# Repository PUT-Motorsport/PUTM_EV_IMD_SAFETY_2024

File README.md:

# Insulation Monitoring Device driver

A driver for Bender ISOMETER IR155-3203 to comply with FSG Rules 25' about latching, and only hard-wired electronics.
As per September 2025 in PMX Malta it relies only on Bender "IMD OK" signal, no PWM reading part needed

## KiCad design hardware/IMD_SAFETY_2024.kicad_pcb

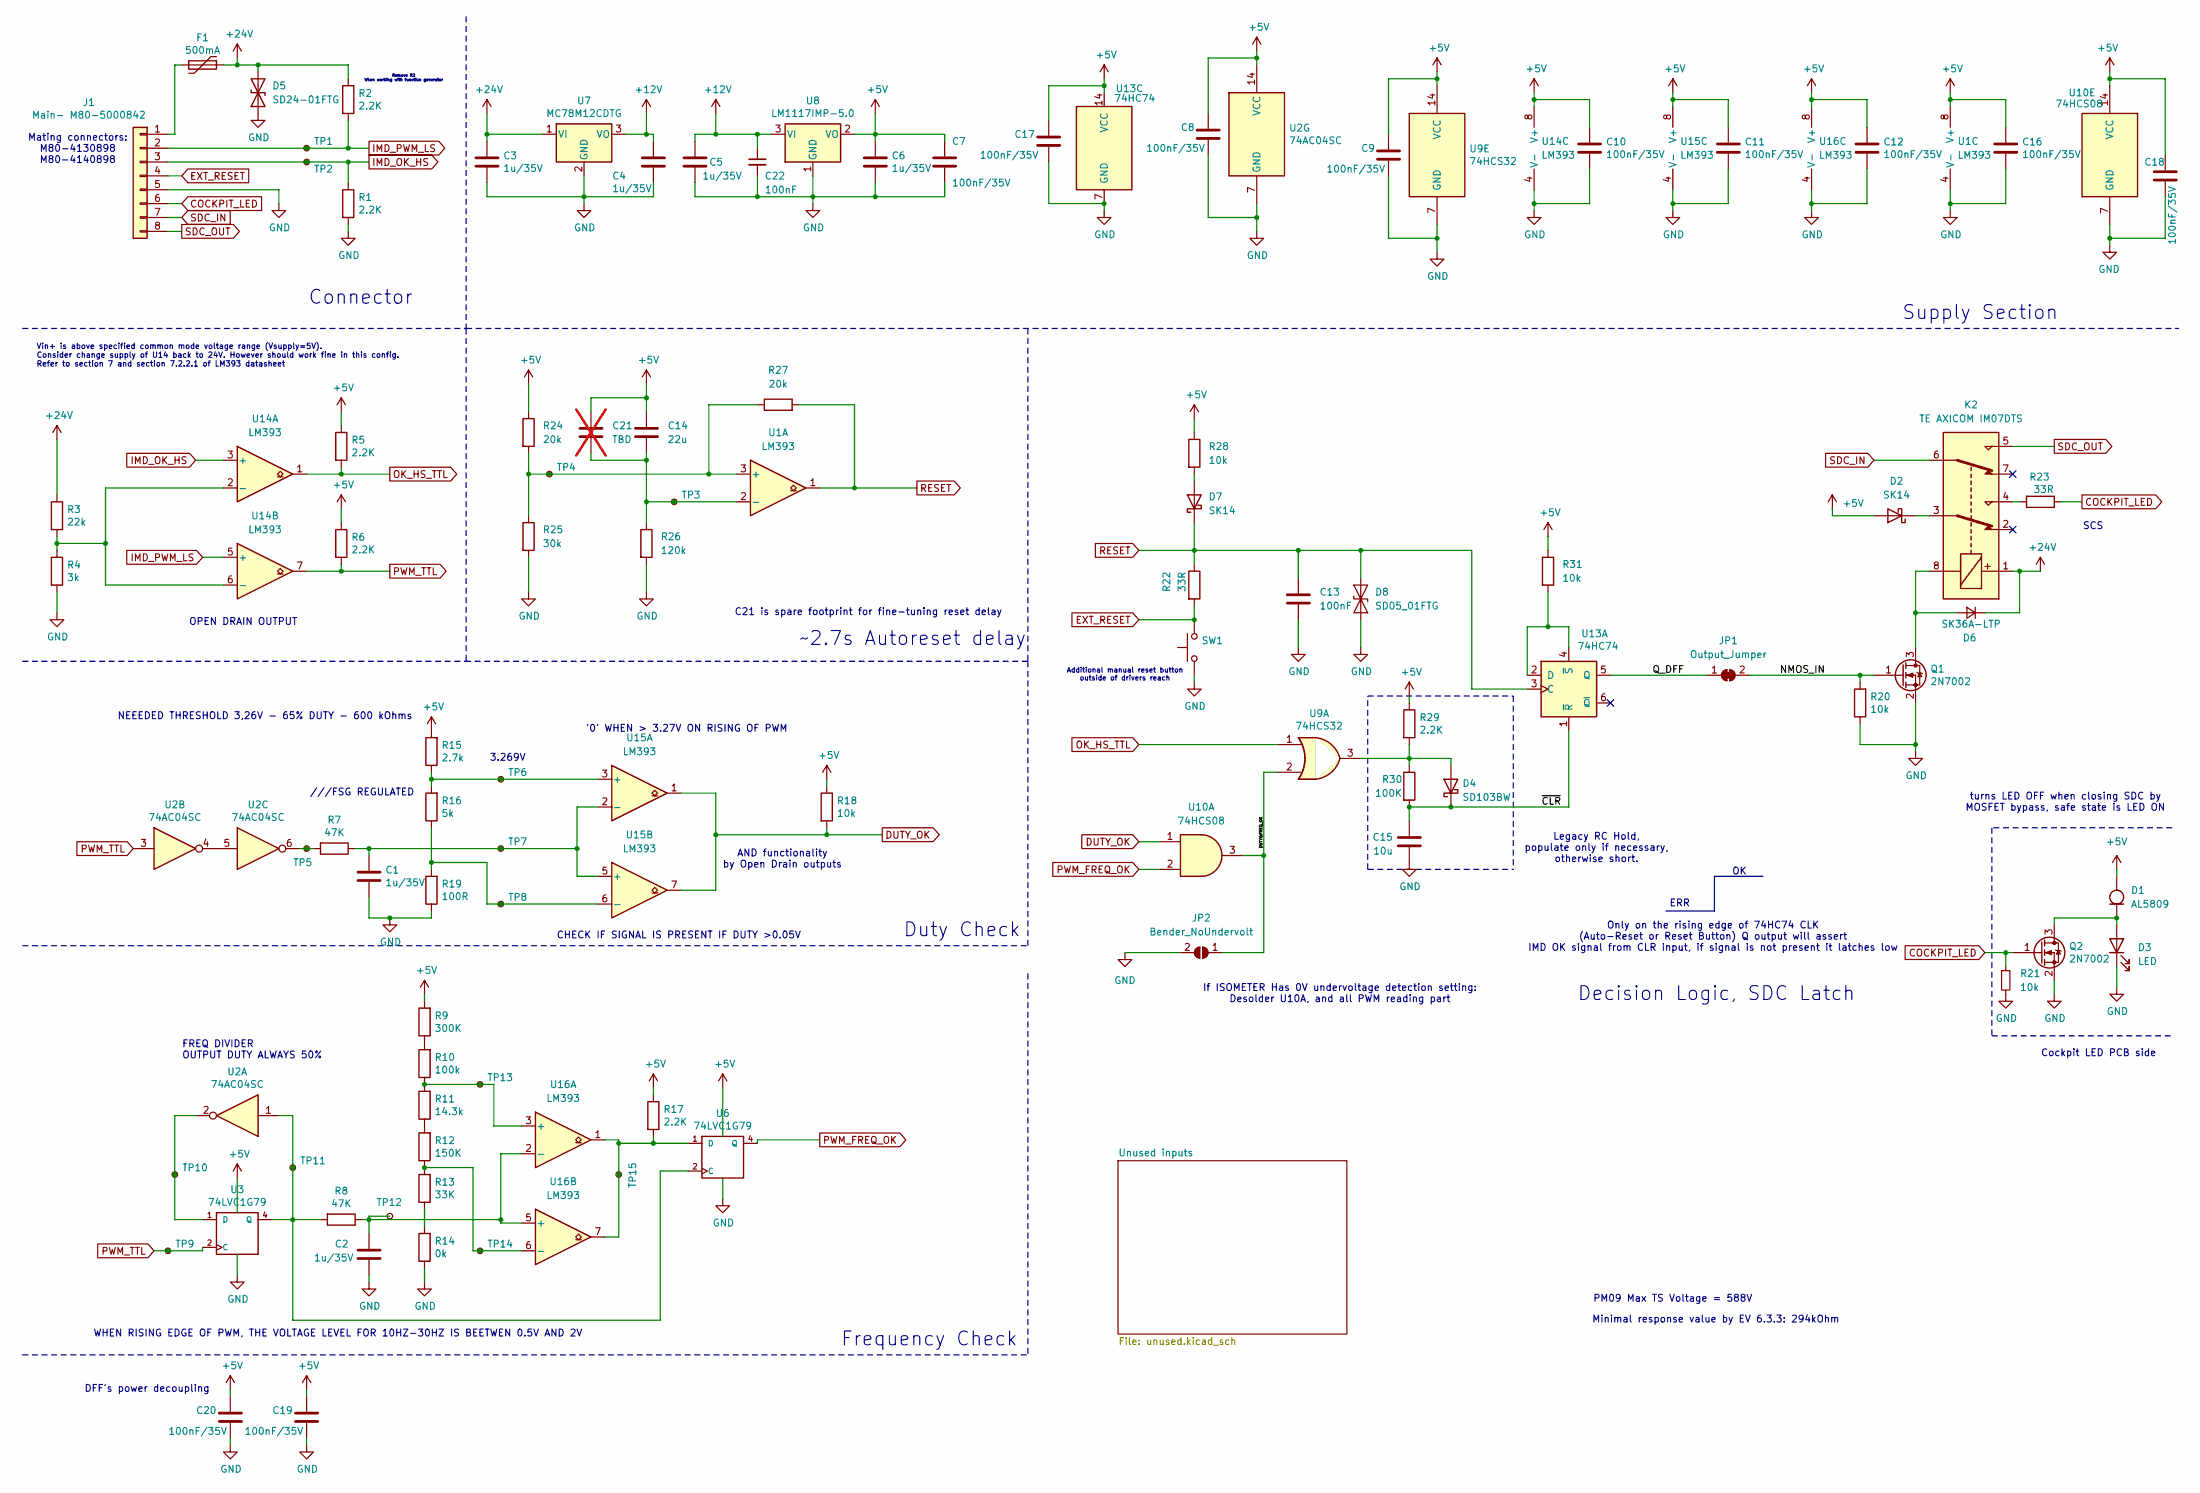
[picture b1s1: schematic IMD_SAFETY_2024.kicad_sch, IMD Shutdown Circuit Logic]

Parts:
C1, C2, C3, C4, C5, C6: 1u/35V; C_0805_2012Metric
C7, C8, C9, C10, C11, C12, C16, C17, C18, C19, C20: 100nF/35V; C_0603_1608Metric
C13: 100nF; C_0603_1608Metric_Pad1.08x0.95mm_HandSolder
C14: 22u; C_1206_3216Metric; Mouser# 187-CL31A226KOHNNWE
C15: 10u; C_1206_3216Metric; Mouser# 187-CL31A106MQHNNNE
C21: TBD; C_1206_3216Metric; not fitted
C22: 100nF; C_0603_1608Metric
D1: AL5809
D2, D7: SK14; D_SMA; Mouser# 637-SK14
D3: LED
D4: SD103BW; D_SOD-123F; Mouser# 637-SD103BW
D5: SD24-01FTG; SOD2613X114N
D6: SK36A-LTP; DIOM5226X244N; Mouser# 833-SK36A-LTP
D8: SD05_01FTG; D_SOD-323
F1: 500mA; Fuse_1206_3216Metric; Mouser# 576-1206L050/24WR
J1: Main- M80-5000842; M80-50008YY_2
JP1: Output_Jumper; SolderJumper-2_P1.3mm_Open_Pad1.0x1.5mm
JP2: Bender_NoUndervolt; SolderJumper-2_P1.3mm_Open_Pad1.0x1.5mm
K2: TE AXICOM IM07DTS; IM23TS
Q1: 2N7002; SOT-23; Mouser# 726-2N7002H6327XTSA2
Q2: 2N7002; SOT-23
R1, R2, R5, R6, R17, R29: 2.2K; R_0603_1608Metric
R3: 22k; R_0603_1608Metric
R4: 3k; R_0603_1608Metric
R7, R8: 47K; R_0603_1608Metric
R9: 300K; R_0603_1608Metric
R10: 100k; R_0603_1608Metric
R11: 14.3k; R_0603_1608Metric
R12: 150K; R_0603_1608Metric
R13: 33K; R_0603_1608Metric
R14: 0k; R_0603_1608Metric
R15: 2.7k; R_0603_1608Metric
R16: 5k; R_0603_1608Metric
R18, R20, R28, R31: 10k; R_0603_1608Metric
R19: 100R; R_0603_1608Metric
R21: 10k
R22, R23: 33R; R_0805_2012Metric
R24, R27: 20k; R_0603_1608Metric
R25: 30k; R_0603_1608Metric
R26: 120k; R_0603_1608Metric
R30: 100K; R_0603_1608Metric
SW1: Push Button
TP1, TP2, TP3, TP4, TP5, TP6, TP7, TP8, TP9, TP10, TP11, TP12, TP13, TP14, TP15: TestPoint_Small; TestPoint_Pad_D1.0mm
U1, U14, U15, U16: LM393; SOIC127P600X175-8N; Mouser# 595-LM393ADR
U2: 74AC04SC; SOIC-14_3.9x8.7mm_P1.27mm; Mouser# 512-74AC04SC
U3, U6: 74LVC1G79; SOT-23-5; Mouser# 595-SN74LVC1G79DBVR
U7: MC78M12CDTG; TO-252-3_TabPin2; Mouser# 863-MC7812ACD2TR4G
U8: LM1117IMP-5.0; SOT-223-3_TabPin2; Mouser# 926-LM1117IMPX50NOPB
U9: 74HCS32; SOP65P640X120-14N; Mouser# 595-SN74HCS32PWR
U10: 74HCS08; SOP65P640X120-14N; Mouser# 595-SN74HCS08PWR
U13: 74HC74; SOP65P640X120-14N

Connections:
+5V: C6.1, C7.1, C8.1, C9.1, C10.1, C11.1, C12.1, C14.1, C16.1, C17.1, C18.1, C19.1, C20.1, C21.1, D1.2 (A), D2.2 (A), R5.1, R6.1, R9.2, R15.2, R17.1, R18.1, R24.1, R28.1, R29.1, R31.1, U1.8 (V+), U2.14 (VCC), U3.5 (VCC), U6.5 (VCC), U8.2 (VO), U9.14 (VCC), U10.14 (VCC), U13.14 (VCC), U14.8 (V+), U15.8 (V+), U16.8 (V+); also elsewhere on the board
+12V: C4.1, C5.1, C22.1, U7.3 (VO), U8.3 (VI)
+24V: C3.1, D5.2 (A2), D6.1 (K), F1.1, K2.1, R2.1, R3.1, U7.1 (VI)
/DUTY&FREQ_OK: JP2.1 (A), U9.2, U10.3
/NMOS_IN: JP1.2 (B), Q1.1 (G), R20.2
/Q_DFF: JP1.1 (A), U13.5 (Q)
/~CLR: C15.1, D4.1 (K), R30.2, U13.1 (~R)
COCKPIT_LED: J1.6, Q2.1 (G), R21.1, R23.1
DUTY_OK: R18.2, U10.1, U15.1, U15.7
EXT_RESET: J1.4, R22.2, SW1.2
GND: C1.2, C2.2, C3.2, C4.2, C5.2, C6.2, C7.2, C8.2, C9.2, C10.2, C11.2, C12.2, C13.2, C15.2, C16.2, C17.2, C18.2, C19.2, C20.2, C22.2, D3.1 (K), D5.1 (A1), D8.2 (A2), J1.5, JP2.2 (B), Q1.2 (S), Q2.2 (S), R1.2, R4.2, R14.1, R19.1, R20.1, R21.2, R25.2, R26.2, SW1.1, U1.4 (V-), U2.7 (GND), U3.3 (GND), U6.3 (GND), U7.2 (GND), U8.1 (GND), U9.7 (GND), U10.7 (GND), U13.7 (GND), U14.4 (V-), U15.4 (V-), U16.4 (V-); also elsewhere on the board
IMD_OK_HS: J1.3, R1.1, TP2.1, U14.3 (+)
IMD_PWM_LS: J1.2, R2.2, TP1.1, U14.5 (+)
unnamed: D1.1 (K), D3.2 (A), Q2.3 (D)
unnamed: D2.1 (K), K2.3
unnamed: D4.2 (A), R29.2, R30.1, U9.3
unnamed: D6.2 (A), K2.8, Q1.3 (D)
unnamed: D7.2 (A), R28.2
unnamed: F1.2, J1.1
unnamed: K2.4, R23.2
unnamed: R7.2, TP5.1, U2.6
unnamed: R9.1, R10.2
unnamed: R11.1, R12.2
unnamed: R13.1, R14.2
unnamed: R24.2, R25.1, R27.1, TP4.1, U1.3 (+)
unnamed: C14.2, C21.2, R26.1, TP3.1, U1.2 (-)
unnamed: U2.4, U2.5
unnamed: TP10.1, U2.2, U3.1 (D)
unnamed: R8.2, TP11.1, U2.1, U3.4 (Q), U6.2 (C)
unnamed: R17.2, TP15.1, U6.1 (D), U16.1, U16.7
unnamed: R31.2, U13.2 (D), U13.4 (~S)
unnamed: R3.2, R4.1, U14.2 (-), U14.6 (-)
unnamed: R15.1, R16.2, TP6.1, U15.3 (+)
unnamed: C1.1, R7.1, TP7.1, U15.2 (-), U15.5 (+)
unnamed: R16.1, R19.2, TP8.1, U15.6 (-)
unnamed: R10.1, R11.2, TP13.1, U16.3 (+)
unnamed: C2.1, R8.1, TP12.1, U16.2 (-), U16.5 (+)
unnamed: R12.1, R13.2, TP14.1, U16.6 (-)
OK_HS_TTL: R5.2, U9.1, U14.1
PWM_FREQ_OK: U6.4 (Q), U10.2
PWM_TTL: R6.2, TP9.1, U2.3, U3.2 (C), U14.7
RESET: C13.1, D7.1 (K), D8.1 (A1), R22.1, R27.2, U1.1, U13.3 (C)
SDC_IN: J1.7, K2.6
SDC_OUT: J1.8, K2.5

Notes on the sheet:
Minimal response value by EV 6.3.3: 294kOhm
C21 is spare footprint for fine-tuning reset delay
FREQ DIVIDER OUTPUT DUTY ALWAYS 50%
///FSG REGULATED
Decision Logic, SDC Latch
WHEN RISING EDGE OF PWM, THE VOLTAGE LEVEL FOR 10HZ-30HZ IS BEETWEN 0.5V AND 2V
~2.7s Autoreset delay
Legacy RC Hold, populate only if necessary, otherwise short.
DFF's power decoupling
ERR
CHECK IF SIGNAL IS PRESENT IF DUTY >0.05V
Remove R2 When working with function generator
Cockpit LED PCB side
3.269V
PM09 Max TS Voltage = 588V
Mating connectors: M80-4130898 M80-4140898
'0' WHEN > 3.27V ON RISING OF PWM
Additional manual reset button outside of drivers reach
If ISOMETER Has 0V undervoltage detection setting: Desolder U10A, and all PWM reading part
AND functionality by Open Drain outputs
OPEN DRAIN OUTPUT
Frequency Check
Supply Section
Duty Check
turns LED OFF when closing SDC by MOSFET bypass, safe state is LED ON
NEEEDED THRESHOLD 3,26V - 65% DUTY - 600 kOhms
SCS
Connector
Vin+ is above specified common mode voltage range (Vsupply=5V). Consider change supply of U14 back to 24V. However should work fine in this config. Refer to section 7 and section 7.2.2.1 of LM393 datasheet
Only on the rising edge of 74HC74 CLK (Auto-Reset or Reset Button) Q output will assert IMD OK signal from CLR input, if signal is not present it latches low

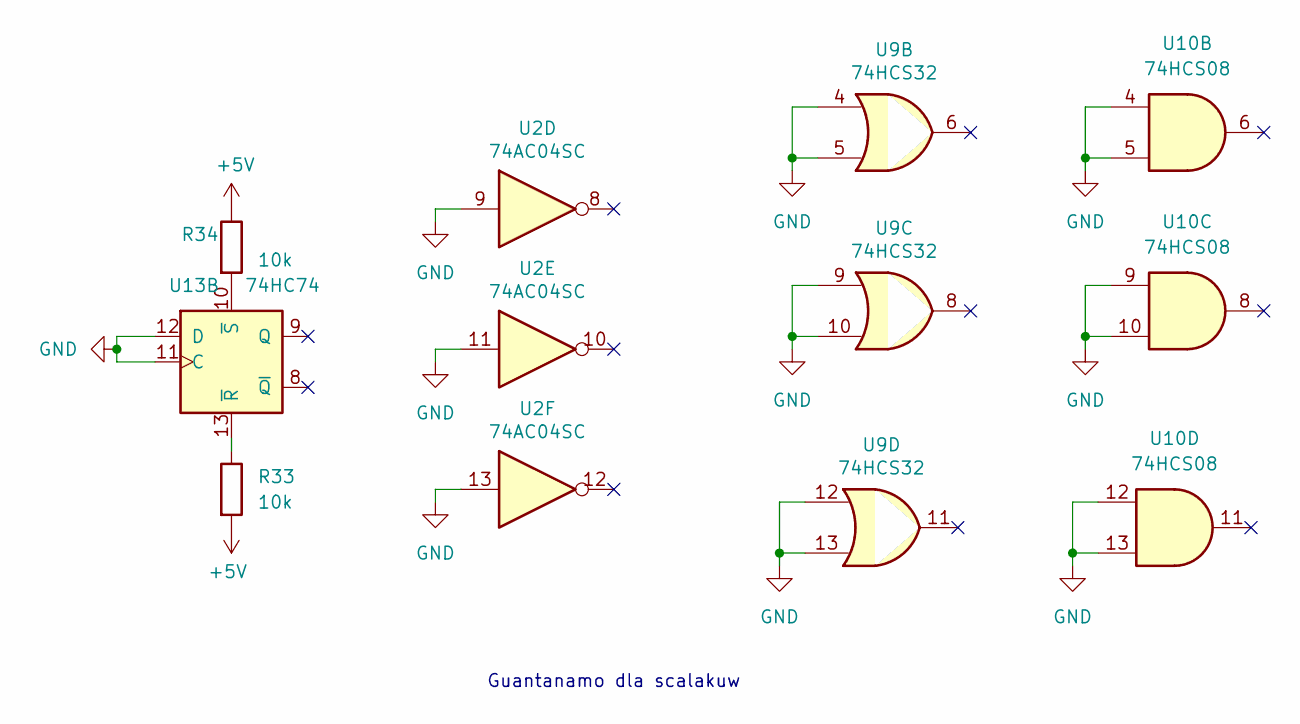
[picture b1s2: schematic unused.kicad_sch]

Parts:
R33, R34: 10k; R_0603_1608Metric
U2: 74AC04SC; SOIC-14_3.9x8.7mm_P1.27mm; Mouser# 512-74AC04SC
U9: 74HCS32; SOP65P640X120-14N; Mouser# 595-SN74HCS32PWR
U10: 74HCS08; SOP65P640X120-14N; Mouser# 595-SN74HCS08PWR
U13: 74HC74; SOP65P640X120-14N

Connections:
+5V: R33.2, R34.1; also elsewhere on the board
GND: U2.9, U2.11, U2.13, U9.4, U9.5, U9.9, U9.10, U9.12, U9.13, U10.4, U10.5, U10.9, U10.10, U10.12, U10.13, U13.11 (C), U13.12 (D); also elsewhere on the board
unnamed: R33.1, U13.13 (~R)
unnamed: R34.2, U13.10 (~S)

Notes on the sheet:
Guantanamo dla scalakuw

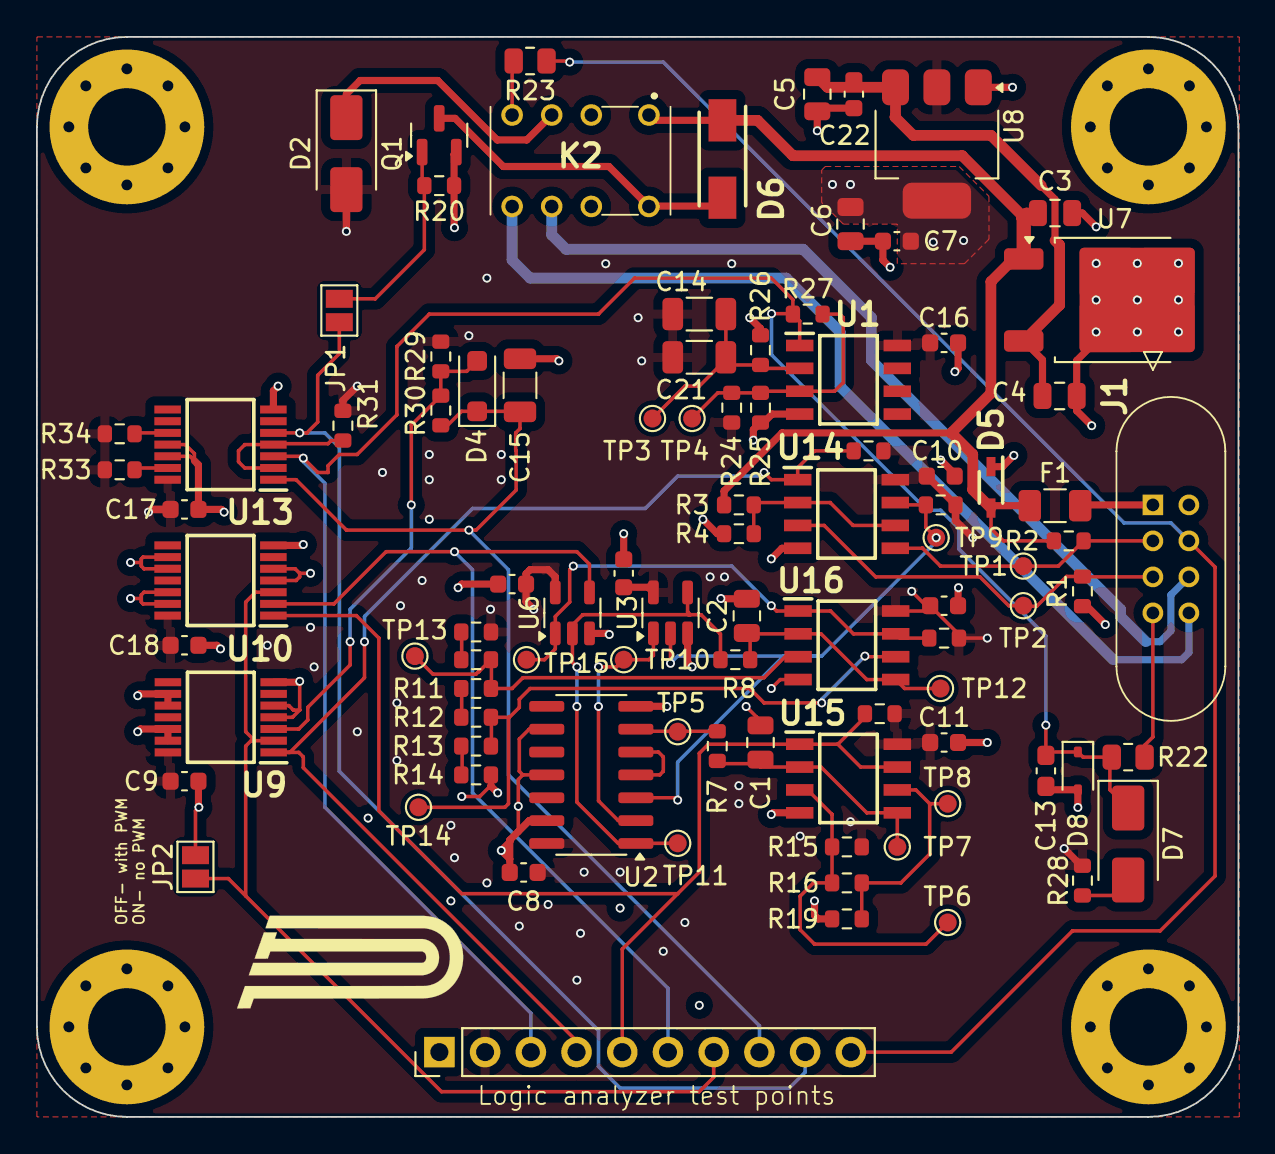
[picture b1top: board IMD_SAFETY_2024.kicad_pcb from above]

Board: 4 copper layers, 66.8 x 60.0 mm, 93 parts (0 on the bottom side), 45 nets.

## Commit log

2024-03-11 add new autoreset simulation draft
2024-04-09 ESF schematic version, relay switched to AXICOM
2024-04-09 Remove redundant files
2024-04-12 IC footprints assign
2024-04-16 Passives footprint assignment
2024-04-24 WIP Layout
2024-04-25 WIP Routing
2024-04-28 0xDRC, ready for review
2024-04-29 Production Files
2024-06-08 Updated R3 R4 Values
2024-08-16 FSG fuckup comment
2024-10-12 Add reset line transient surpression
2024-10-14 OxDRC state, 2.1.0 ready to review, change connector to vertical, and R-Reset node slightly
2024-10-15 2.1.0 Release, adjust after review
2024-11-26 Add 0V jumper
2025-03-15 Add input stage LM393 comment
